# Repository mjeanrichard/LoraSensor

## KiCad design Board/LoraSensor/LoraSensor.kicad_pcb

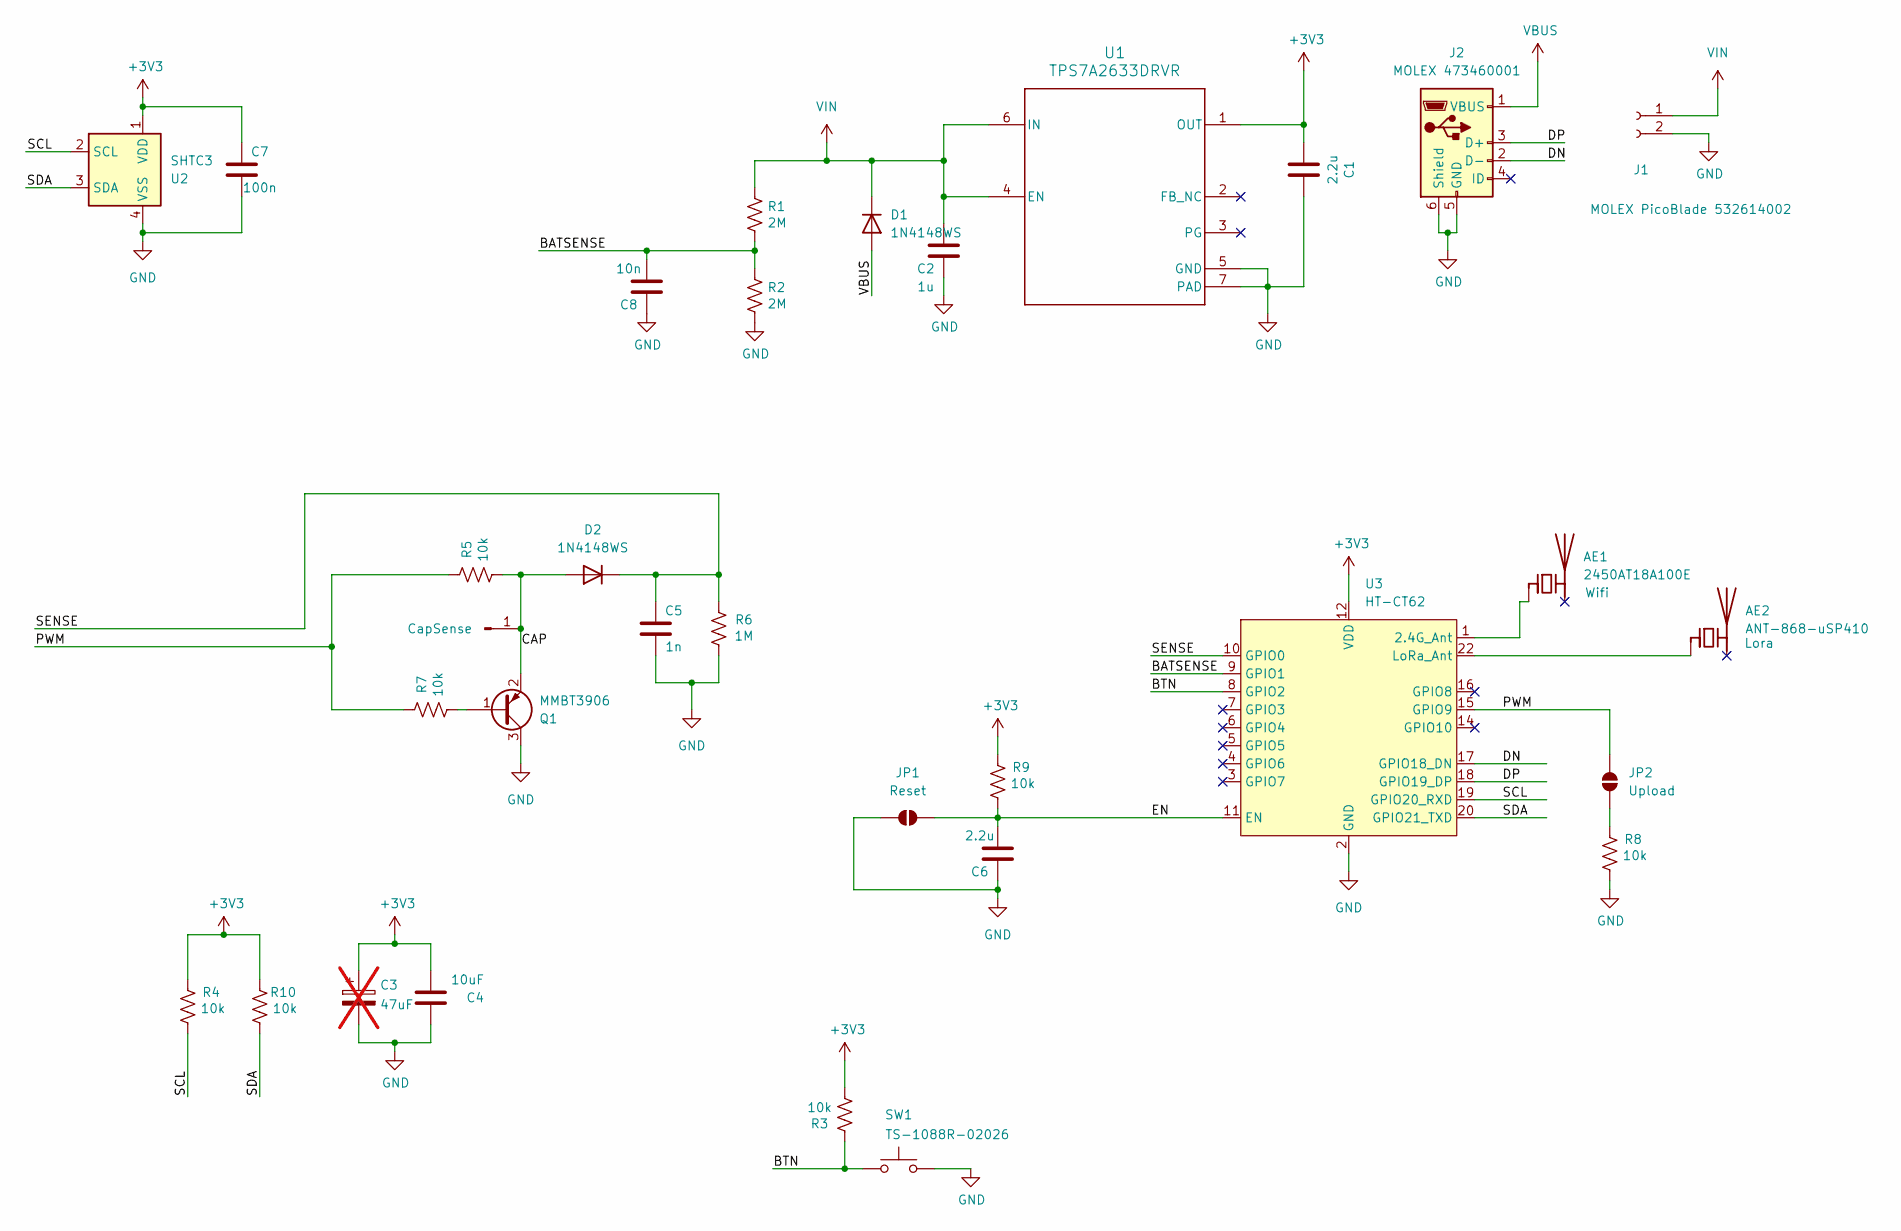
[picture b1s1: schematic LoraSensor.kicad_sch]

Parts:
AE1: 2450AT18A100E; 2450AT18A100E_JOT
AE2: ANT-868-uSP410
C1, C6: 2.2u; C_0805_2012Metric_Pad1.18x1.45mm_HandSolder
C2: 1u; C_0805_2012Metric_Pad1.18x1.45mm_HandSolder
C3: 47uF; CP_EIA-3216-18_Kemet-A_Pad1.58x1.35mm_HandSolder; not fitted
C4: 10uF; C_0805_2012Metric_Pad1.18x1.45mm_HandSolder
C5: 1n; C_0805_2012Metric_Pad1.18x1.45mm_HandSolder
C7: 100n; C_0805_2012Metric_Pad1.18x1.45mm_HandSolder
C8: 10n; C_0805_2012Metric_Pad1.18x1.45mm_HandSolder
D1, D2: 1N4148WS; D_SOD-323
J1: MOLEX PicoBlade 532614002; 532614002
J2: MOLEX 473460001; USB_Micro-B_Molex_47346-0001
J4: CapSense
JP1: Reset; SolderJumper-2_P1.3mm_Open_RoundedPad1.0x1.5mm
JP2: Upload; SolderJumper-2_P1.3mm_Open_RoundedPad1.0x1.5mm
Q1: MMBT3906; SOT-23
R1, R2: 2M; R_1206_3216Metric
R3, R4, R5, R7, R8, R9, R10: 10k; R_1206_3216Metric
R6: 1M; R_1206_3216Metric
SW1: TS-1088R-02026; smd-tactile
U1: TPS7A2633DRVR; TI_WSON-6-1EP_2x2mm_P0.65mm_EP1x1.6mm
U2: SHTC3; Sensirion_DFN-4-1EP_2x2mm_P1mm_EP0.7x1.6mm
U3: HT-CT62; Heltec_HT-CT62

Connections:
+3V3: C1.2, C3.1, C4.2, C7.1, R3.2, R4.2, R9.2, R10.2, U1.1 (OUT), U2.1 (VDD), U3.12 (VDD)
/BATSENSE: C8.2, R1.2, R2.2, U3.9 (GPIO1)
/BTN: R3.1, SW1.1, U3.8 (GPIO2)
/CAP: D2.2 (A), J4.1, Q1.2 (E), R5.2
/DN: J2.2 (D-), U3.17 (GPIO18_DN)
/DP: J2.3 (D+), U3.18 (GPIO19_DP)
/EN: C6.2, JP1.2 (B), R9.1, U3.11 (EN)
/PWM: JP2.2 (B), R5.1, R7.1, U3.15 (GPIO9)
/SCL: R4.1, U2.2 (SCL), U3.19 (GPIO20_RXD)
/SDA: R10.1, U2.3 (SDA), U3.20 (GPIO21_TXD)
/SENSE: C5.1, D2.1 (K), R6.1, U3.10 (GPIO0)
GND: C1.1, C2.1, C3.2, C4.1, C5.2, C6.1, C7.2, C8.1, J1.2, J2.5 (GND), J2.6 (Shield), JP1.1 (A), Q1.3 (C), R2.1, R6.2, R8.1, SW1.2, U1.5 (GND), U1.7 (PAD), U2.4 (VSS), U3.2 (GND), U3.13 (GND), U3.21 (GND)
unnamed: AE1.1 (FEED), U3.1 (2.4G_Ant)
unnamed: AE2.1 (FEED), U3.22 (LoRa_Ant)
unnamed: JP2.1 (A), R8.2
unnamed: Q1.1 (B), R7.2
VBUS: D1.2 (A), J2.1 (VBUS)
VIN: C2.2, D1.1 (K), J1.1, R1.1, U1.4 (EN), U1.6 (IN)

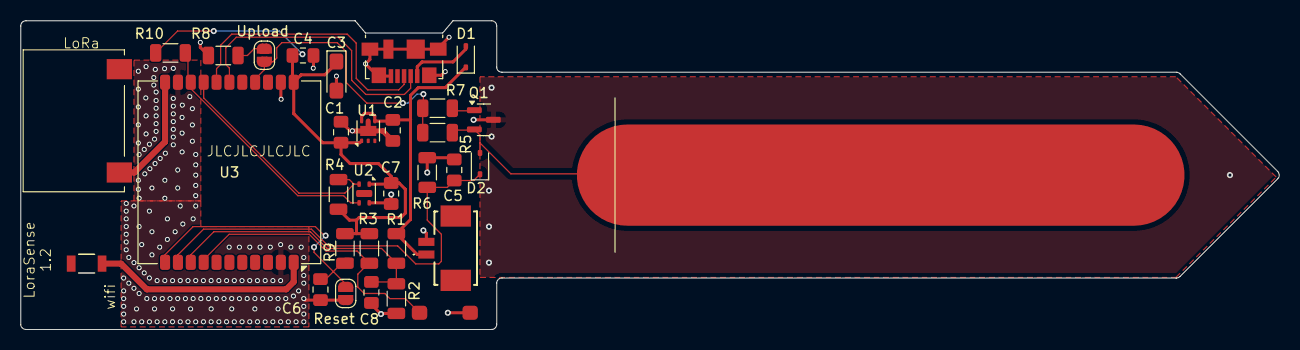
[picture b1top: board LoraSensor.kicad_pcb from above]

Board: 2 copper layers, 124.2 x 30.5 mm, 32 parts (0 on the bottom side), 18 nets.

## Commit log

2024-06-06 Initial Firmware
2024-06-20 PCB V1.1
2024-06-26 Version 1.1
2024-07-07 PCB Version 1.2
2024-10-26 Firmware Improvements
2026-06-19 fix: bugs
2026-06-19 fix: minor fixes
2026-06-20 fix add firmware version
2026-06-20 add github actions
2026-06-21 fix: github action
2026-06-22 fix: first wifi implementation
2026-06-22 fix: remove components
2026-06-22 fix: minor issues
2026-06-22 fix: publish firmware.
2026-06-22 release: v1.1
2026-06-22 release: v1.2
2026-06-22 release: v1.3
